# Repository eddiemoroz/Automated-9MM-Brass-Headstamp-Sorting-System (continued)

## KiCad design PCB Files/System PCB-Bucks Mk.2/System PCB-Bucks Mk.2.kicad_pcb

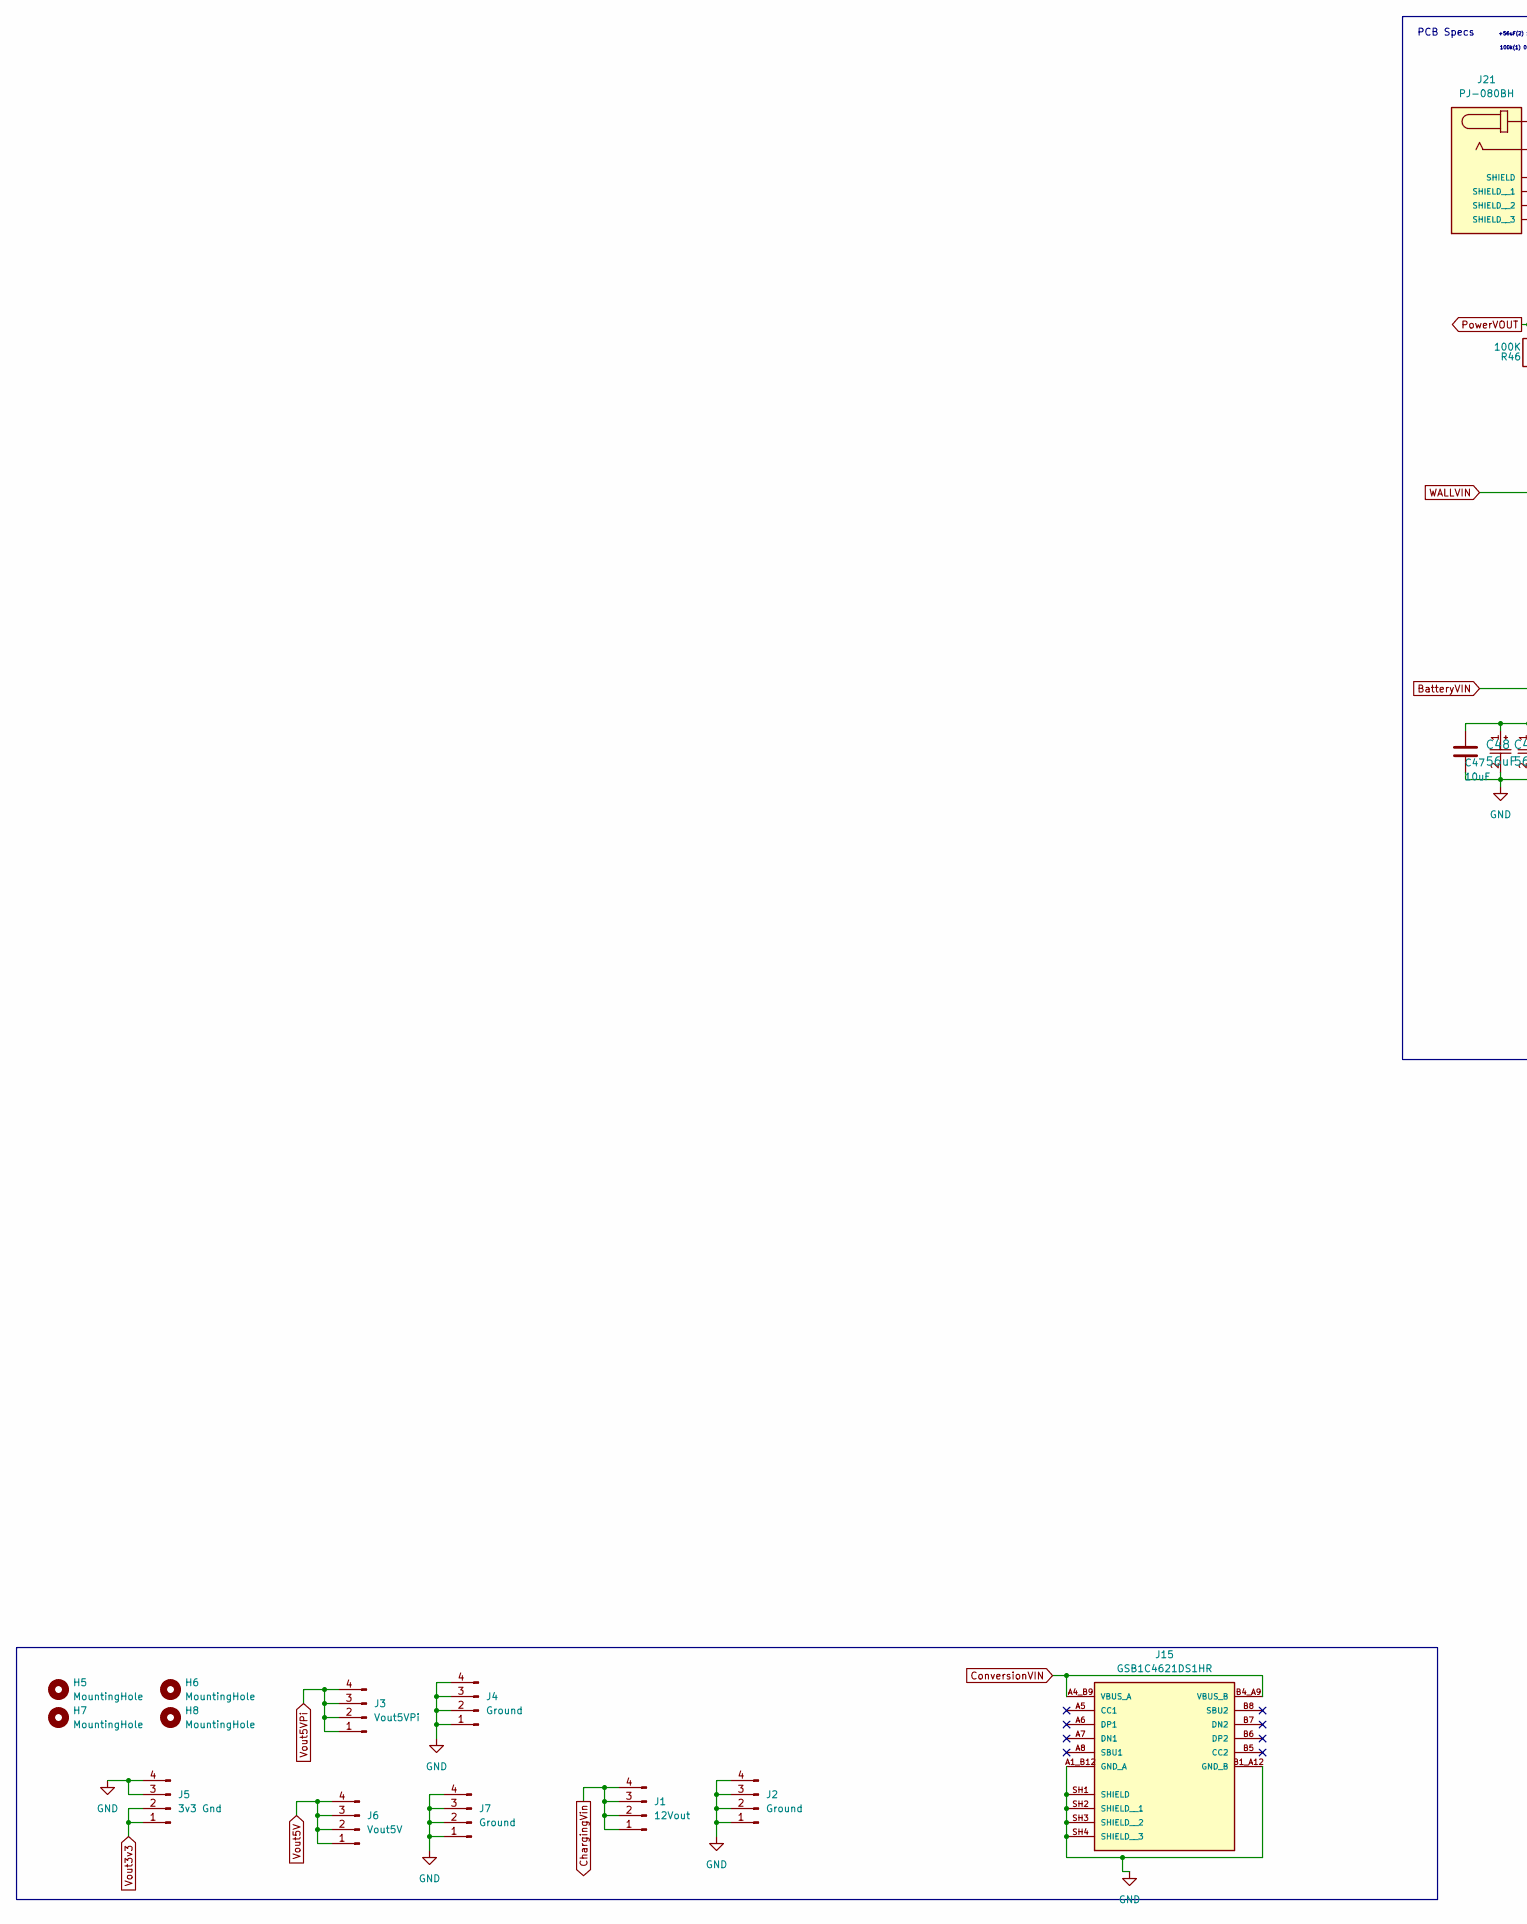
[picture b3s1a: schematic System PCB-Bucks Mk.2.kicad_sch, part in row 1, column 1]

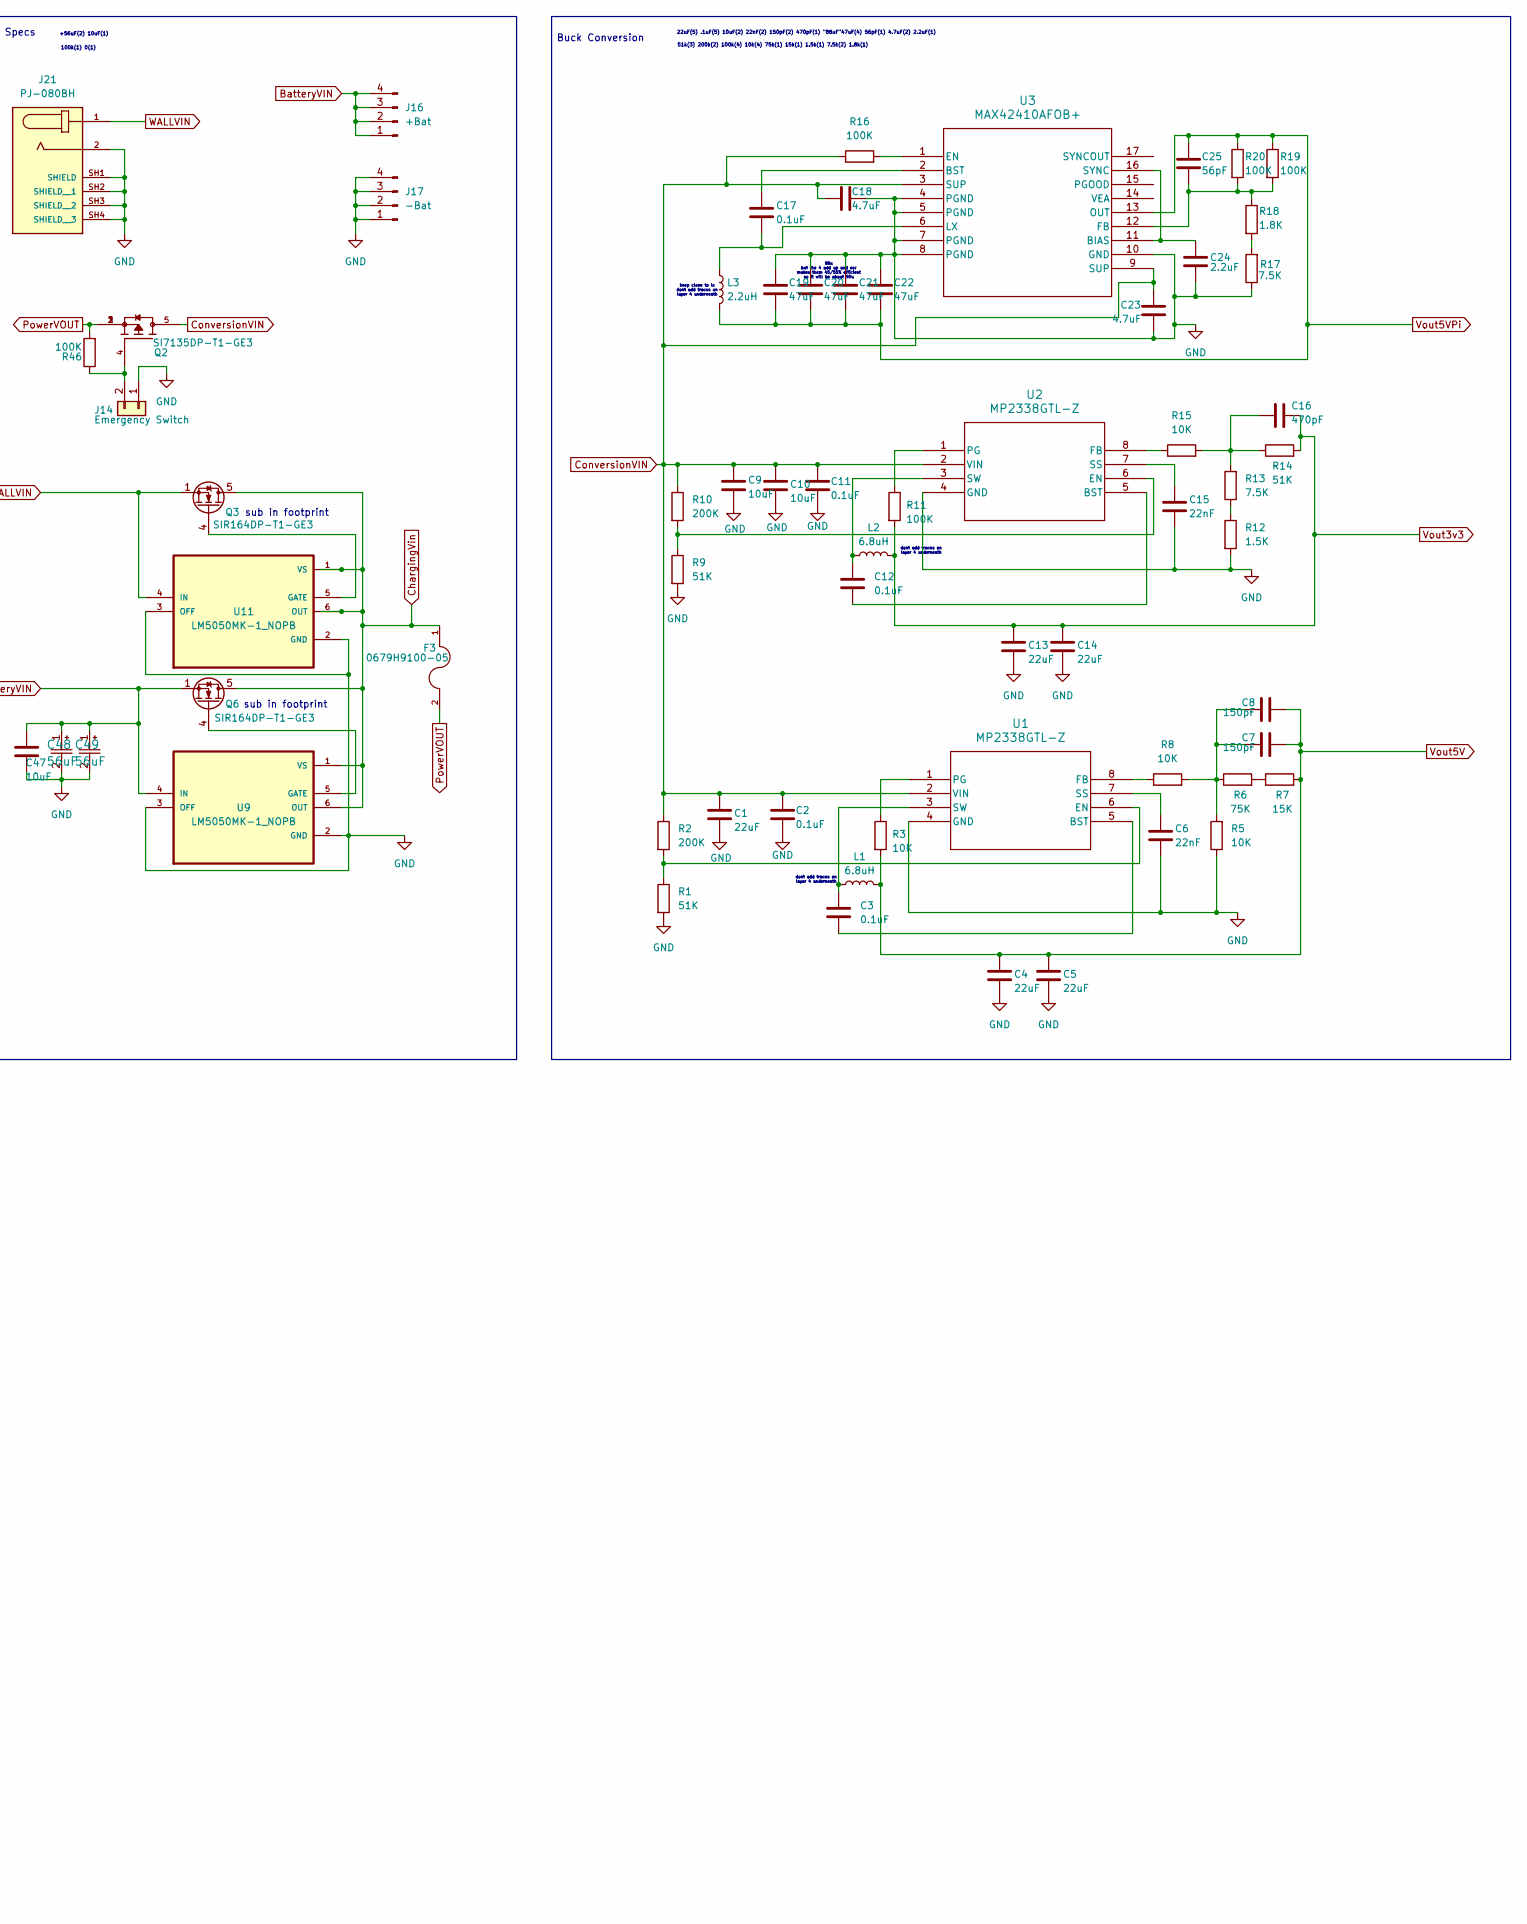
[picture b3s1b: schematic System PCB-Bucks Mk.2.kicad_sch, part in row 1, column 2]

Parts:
C1, C4, C5, C13, C14: 22uF; C_1210_3225Metric_Pad1.33x2.70mm_HandSolder
C2, C3, C11, C12, C17: 0.1uF; C_0805_2012Metric_Pad1.18x1.45mm_HandSolder
C6, C15: 22nF; C_0805_2012Metric_Pad1.18x1.45mm_HandSolder
C7, C8: 150pF; C_0805_2012Metric_Pad1.18x1.45mm_HandSolder
C9, C10, C47: 10uF; C_1206_3216Metric_Pad1.33x1.80mm_HandSolder
C16: 470pF; C_0805_2012Metric_Pad1.18x1.45mm_HandSolder
C18, C23: 4.7uF; C_1206_3216Metric_Pad1.33x1.80mm_HandSolder
C19, C20, C21, C22: 47uF; C_1210_3225Metric_Pad1.33x2.70mm_HandSolder
C24: 2.2uF; C_0805_2012Metric_Pad1.18x1.45mm_HandSolder
C25: 56pF; C_0402_1005Metric_Pad0.74x0.62mm_HandSolder
C48, C49: 56uF; CAP_GY_6P3X5P8_NCH-M
F3: 0679H9100-05; FUSC6125X279N; PARTREV 0679H Apr2019
H5, H6, H7, H8: MountingHole; MountingHole_3.2mm_M3
J1: 12Vout; FanPinHeader_1x04_P2.54mm_Vertical
J2, J4, J7: Ground; FanPinHeader_1x04_P2.54mm_Vertical
J3: Vout5VPi; FanPinHeader_1x04_P2.54mm_Vertical
J5: 3v3 Gnd; FanPinHeader_1x04_P2.54mm_Vertical
J6: Vout5V; FanPinHeader_1x04_P2.54mm_Vertical
J14: Emergency Switch; PinSocket_1x02_P2.54mm_Vertical
J15: GSB1C4621DS1HR; AMPHENOL_GSB1C4621DS1HR; PARTREV AX1
J16: +Bat; FanPinHeader_1x04_P2.54mm_Vertical
J17: -Bat; FanPinHeader_1x04_P2.54mm_Vertical
J21: PJ-080BH; CUI_PJ-080BH; PARTREV 1.04
L1, L2: 6.8uH; IND_8357068_WRE-M
L3: 2.2uH; IND_SRP1265A-2R2M
Q2: SI7135DP-T1-GE3; TRANS_SI7135DP-T1-GE3; PARTREV A
Q3, Q6: SIR164DP-T1-GE3; PowerPAK_SO-8_Single
R1, R9, R14: 51K; R_1206_3216Metric_Pad1.30x1.75mm_HandSolder
R2, R10: 200K; R_1206_3216Metric_Pad1.30x1.75mm_HandSolder
R3, R5, R8, R15: 10K; R_1206_3216Metric_Pad1.30x1.75mm_HandSolder
R6: 75K; R_1206_3216Metric_Pad1.30x1.75mm_HandSolder
R7: 15K; R_1206_3216Metric_Pad1.30x1.75mm_HandSolder
R11, R16, R19, R20, R46: 100K; R_1206_3216Metric_Pad1.30x1.75mm_HandSolder
R12: 1.5K; R_1206_3216Metric_Pad1.30x1.75mm_HandSolder
R13, R17: 7.5K; R_1206_3216Metric_Pad1.30x1.75mm_HandSolder
R18: 1.8K; R_1206_3216Metric_Pad1.30x1.75mm_HandSolder
U1, U2: MP2338GTL-Z; SOT-583-8
U3: MAX42410AFOB+
U9, U11: LM5050MK-1_NOPB; LM5050MK-1NOPB

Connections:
BatteryVIN: C47.1, C48.1, C49.1, J16.1, J16.2, J16.3, J16.4, Q6.1 (S), Q6.2 (S), Q6.3 (S), U9.4 (IN)
ChargingVin: F3.1, J1.1, J1.2, J1.3, J1.4, Q3.5 (D), Q6.5 (D), U9.1 (VS), U9.6 (OUT), U11.1 (VS), U11.6 (OUT)
ConversionVIN: C1.1, C2.1, C9.1, C10.1, C11.1, C18.2, C23.1, J15.A4_B9 (VBUS_A), J15.B4_A9 (VBUS_B), Q2.5, R2.1, R10.1, R16.1, U1.2 (VIN), U2.2 (VIN), U3.3 (SUP), U3.9 (SUP)
GND: C1.2, C2.2, C4.2, C5.2, C6.2, C9.2, C10.2, C11.2, C13.2, C14.2, C15.2, C18.1, C19.1, C20.1, C21.1, C22.1, C23.2, C24.2, C47.2, C48.2, C49.2, J2.1, J2.2, J2.3, J2.4, J4.1, J4.2, J4.3, J4.4, J5.3, J5.4, J7.1, J7.2, J7.3, J7.4, J14.1, J15.A1_B12 (GND_A), J15.B1_A12 (GND_B), J15.SH1 (SHIELD), J15.SH2 (SHIELD__1), J15.SH3 (SHIELD__2), J15.SH4 (SHIELD__3), J17.1, J17.2, J17.3, J17.4, J21.2, J21.SH1 (SHIELD), J21.SH2 (SHIELD__1), J21.SH3 (SHIELD__2), J21.SH4 (SHIELD__3), R1.2, R5.1, R9.2, R12.2, R17.1, U1.4 (GND), U2.4 (GND), U3.4 (PGND), U3.5 (PGND), U3.7 (PGND), U3.8 (PGND), U3.10 (GND), U9.2 (GND), U9.3 (OFF), U11.2 (GND), U11.3 (OFF)
unnamed: C7.1, C8.1, R5.2, R6.1, R8.2
unnamed: C16.1, R13.2, R14.1, R15.2
unnamed: J14.2, Q2.4, R46.1
unnamed: Q3.4 (G), U11.5 (GATE)
unnamed: Q6.4 (G), U9.5 (GATE)
unnamed: R6.2, R7.1
unnamed: R12.1, R13.1
unnamed: R17.2, R18.2
unnamed: C3.1, U1.5 (BST)
unnamed: R1.1, R2.2, U1.6 (EN)
unnamed: R8.1, U1.8 (FB)
unnamed: R3.1, U1.1 (PG)
unnamed: C6.1, U1.7 (SS)
unnamed: C3.2, L1.1, U1.3 (SW)
unnamed: C12.1, U2.5 (BST)
unnamed: R9.1, R10.2, U2.6 (EN)
unnamed: R15.1, U2.8 (FB)
unnamed: R11.1, U2.1 (PG)
unnamed: C15.1, U2.7 (SS)
unnamed: C12.2, L2.1, U2.3 (SW)
unnamed: C24.1, U3.11 (BIAS), U3.16 (SYNC)
unnamed: C17.1, U3.2 (BST)
unnamed: R16.2, U3.1 (EN)
unnamed: C25.2, R18.1, R19.2, R20.2, U3.12 (FB)
unnamed: C17.2, L3.1, U3.6 (LX)
PowerVOUT: F3.2, Q2.1, Q2.2, Q2.3, R46.2
Vout3v3: C13.1, C14.1, C16.2, J5.1, J5.2, L2.2, R11.2, R14.2
Vout5V: C4.1, C5.1, C7.2, C8.2, J6.1, J6.2, J6.3, J6.4, L1.2, R3.2, R7.2
Vout5VPi: C19.2, C20.2, C21.2, C22.2, C25.1, J3.1, J3.2, J3.3, J3.4, L3.2, R19.1, R20.1, U3.13 (OUT)
WALLVIN: J21.1, Q3.1 (S), Q3.2 (S), Q3.3 (S), U11.4 (IN)

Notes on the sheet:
sub in footprint
Buck Conversion
dont add traces on layer 4 underneath
+56uF(2) 10uF(1)
51k(3) 200k(2) 100k(4) 10k(4) 75k(1) 15k(1) 1.5k(1) 7.5k(2) 1.8k(1)
keep close to lx dont add traces on layer 4 underneath
PCB Specs
22uF(5) .1uF(5) 10uF(2) 22nF(2) 150pF(2) 470pF(1) "88uF"47uF(4) 56pF(1) 4.7uF(2) 2.2uF(1)
88u but the 4 add up and esr makes them 45/55% efficient so it will be about 90u
100k(1) 0(1)

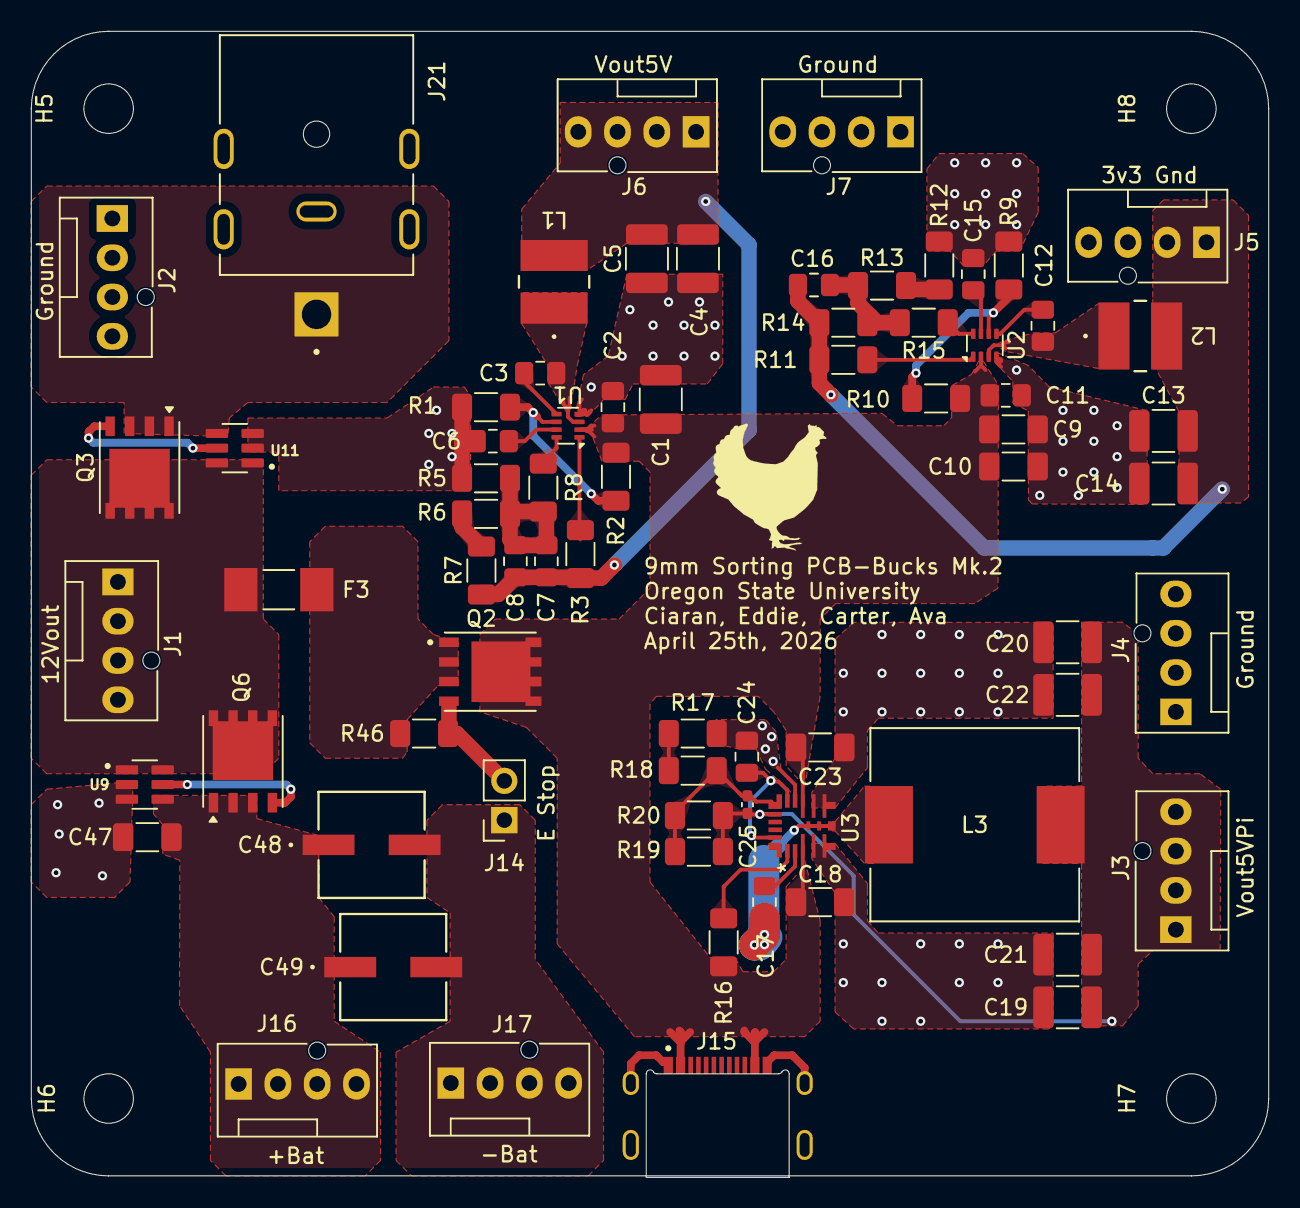
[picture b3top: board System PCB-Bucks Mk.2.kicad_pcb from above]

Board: 2 copper layers, 80.0 x 74.1 mm, 76 parts (0 on the bottom side), 34 nets.

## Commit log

2026-05-16 Artifacts folder + old power PCB
2026-05-16 PCB File Uploads
    Nothing
2026-05-16 PCB File Uploads
2026-05-16 Buck PCB
2026-05-16 Charging PCB
2026-05-16 Controls PCB
2026-05-16 Added Enclosure .STL files
2026-05-16 Added exported Fusion design
2026-05-16 Added Python Code files
    - Includes headstampSorting folder that goes onto the Raspberry Pi 5 and serves as the primary folder
    - Includes training script for model, image processing, and generating datasets
2026-06-04 Added esp .ino files
2026-06-04 Rename System code Mk8.txt to System code Mk8.ino
2026-06-04 Small Name Change
